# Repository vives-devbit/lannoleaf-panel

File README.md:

# LannooLeaf Panel

| Front | Back |
|---|---|
|  |

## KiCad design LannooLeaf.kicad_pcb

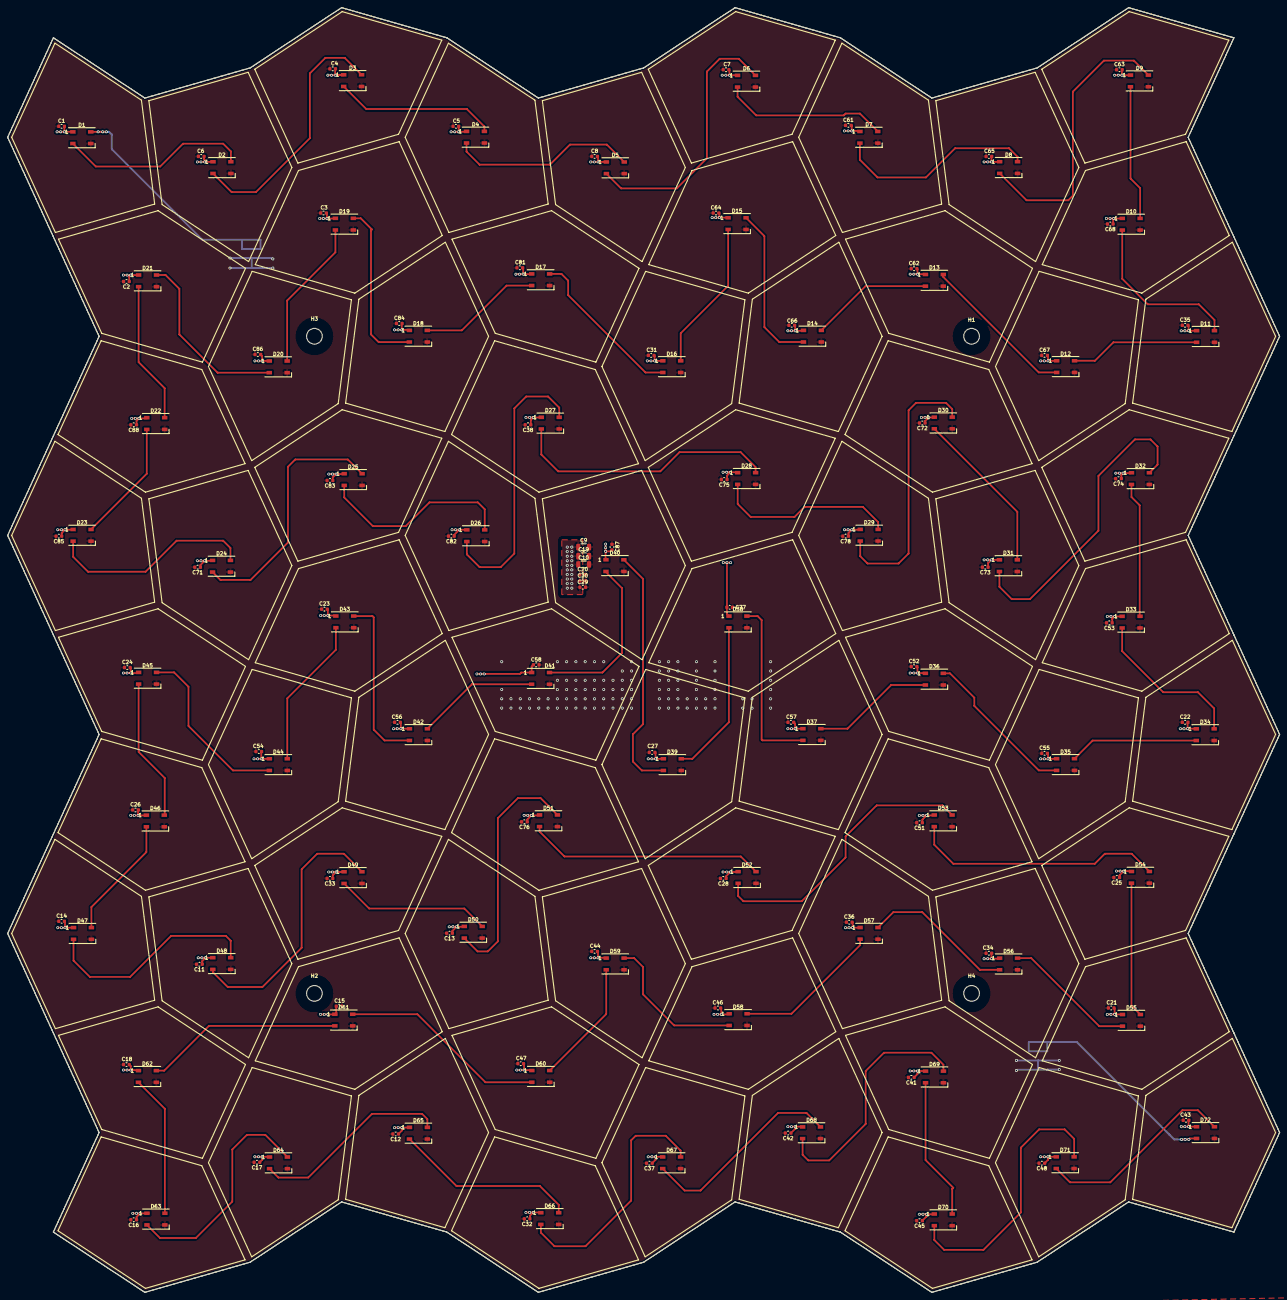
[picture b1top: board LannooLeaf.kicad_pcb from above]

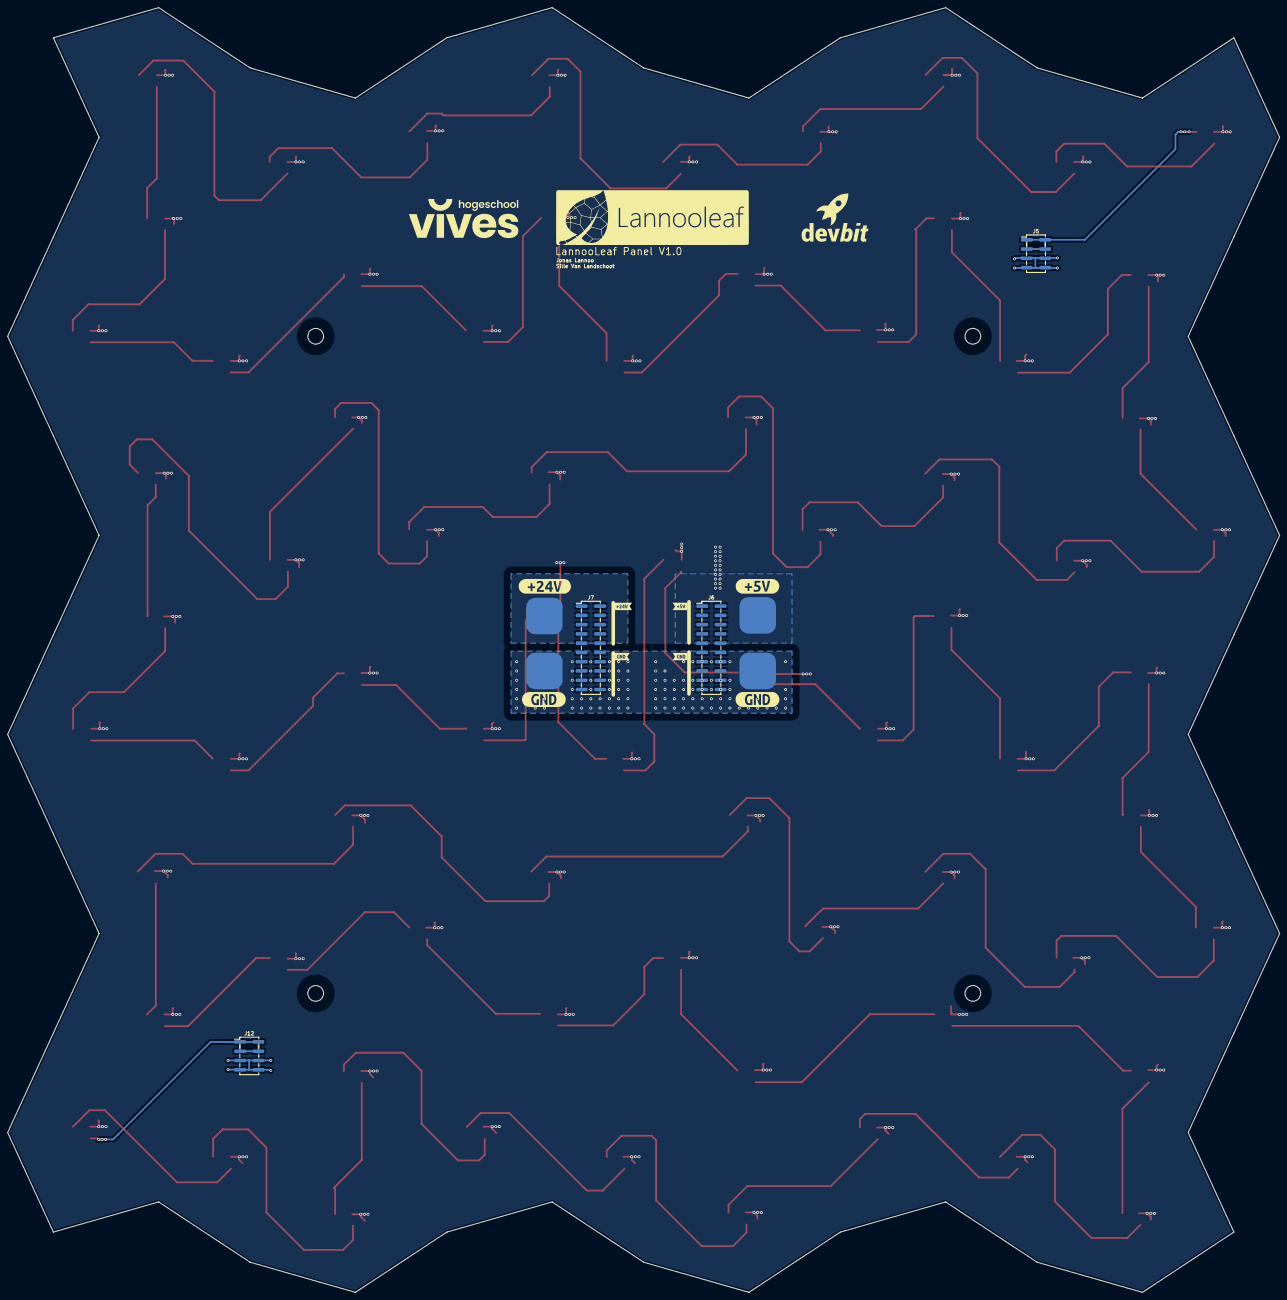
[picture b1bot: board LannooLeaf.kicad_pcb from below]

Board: 2 copper layers, 348.4 x 351.9 mm, 173 parts (19 on the bottom side), 76 nets.

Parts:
C1, C2, C3, C4, C5, C6, C7, C8, C11, C12, C13, C14, C15, C16, C17, C18, C21, C22, C23, C24, C25, C26, C27, C28, C31, C32, C33, C34, C35, C36, C37, C38, C41, C42, C43, C44, C45, C46, C47, C48, C51, C52, C53, C54, C55, C56, C57, C58, C61, C62, C63, C64, C65, C66, C67, C68, C71, C72, C73, C74, C75, C76, C77, C78, C81, C82, C83, C84, C85, C86, C87, C88: 100nF; C_0603_1608Metric
C9, C10, C19: 22uF; C_1206_3216Metric
C20, C29, C30: 1uF; C_0603_1608Metric
D1, D2, D3, D4, D5, D6, D7, D8, D9, D10, D11, D12, D13, D14, D15, D16, D17, D18, D19, D20, D21, D22, D23, D24, D25, D26, D27, D28, D29, D30, D31, D32, D33, D34, D35, D36, D37, D38, D39, D40, D41, D42, D43, D44, D45, D46, D47, D48, D49, D50, D51, D52, D53, D54, D55, D56, D57, D58, D59, D60, D61, D62, D63, D64, D65, D66, D67, D68, D69, D70, D71, D72: WS2812B; LED_WS2812B_PLCC4_5.0x5.0mm_P3.2mm
H1: MountingHole; MountingHole_4.3mm_M4_ISO14580
H2, H3, H4: MountingHole; MountingHole_4.3mm_M4_ISO7380
H5: Logo LannooLeaf; Logo
H6: Logo VIVES; logo-vives
H7: Logo DevBit; logo_devbit_15mm
J1, J2, J3, J4: Conn_01x01; Powerpad
J5, J12: Conn_02x04_Counter_Clockwise; PinHeader_2x04_P2.54mm_Vertical_SMD
J6, J7: Conn_02x10_Counter_Clockwise; PinHeader_2x10_P2.54mm_Vertical_SMD
kibuzzard-62A843C0: G***; kibuzzard-62A843C0
kibuzzard-62A843EA: G***; kibuzzard-62A843EA
kibuzzard-62A8323F: G***; kibuzzard-62A8323F
kibuzzard-62A8324B: G***; kibuzzard-62A8324B
kibuzzard-62A8325B: G***; kibuzzard-62A8325B
kibuzzard-62A8326A: G***; kibuzzard-62A8326A
kibuzzard-62A8440B: G***; kibuzzard-62A8440B
kibuzzard-62A84432: G***; kibuzzard-62A84432

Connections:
+5V: C1.1, C2.1, C3.1, C4.1, C5.1, C6.1, C7.1, C8.1, C9.1, C10.1, C11.1, C12.1, C13.1, C14.1, C15.1, C16.1, C17.1, C18.1, C19.1, C20.1, C21.1, C22.1, C23.1, C24.1, C25.1, C26.1, C27.1, C28.1, C29.1, C30.1, C31.1, C32.1, C33.1, C34.1, C35.1, C36.1, C37.1, C38.1, C41.1, C42.1, C43.1, C44.1, C45.1, C46.1, C47.1, C48.1, C51.1, C52.1, C53.1, C54.1, C55.1, C56.1, C57.1, C58.1, C61.1, C62.1, C63.1, C64.1, C65.1, C66.1, C67.1, C68.1, C71.1, C72.1, C73.1, C74.1, C75.1, C76.1, C77.1, C78.1, C81.1, C82.1, C83.1, C84.1, C85.1, C86.1, C87.1, C88.1, D1.1 (VDD), D2.1 (VDD), D3.1 (VDD), D4.1 (VDD), D5.1 (VDD), D6.1 (VDD), D7.1 (VDD), D8.1 (VDD), D9.1 (VDD), D10.1 (VDD), D11.1 (VDD), D12.1 (VDD), D13.1 (VDD), D14.1 (VDD), D15.1 (VDD), D16.1 (VDD), D17.1 (VDD), D18.1 (VDD), D19.1 (VDD), D20.1 (VDD), D21.1 (VDD), D22.1 (VDD), D23.1 (VDD), D24.1 (VDD), D25.1 (VDD), D26.1 (VDD), D27.1 (VDD), D28.1 (VDD), D29.1 (VDD), D30.1 (VDD), D31.1 (VDD), D32.1 (VDD), D33.1 (VDD), D34.1 (VDD), D35.1 (VDD), D36.1 (VDD), D37.1 (VDD), D38.1 (VDD), D39.1 (VDD), D40.1 (VDD), D41.1 (VDD), D42.1 (VDD), D43.1 (VDD), D44.1 (VDD), D45.1 (VDD), D46.1 (VDD), D47.1 (VDD), D48.1 (VDD), D49.1 (VDD), D50.1 (VDD), D51.1 (VDD), D52.1 (VDD), D53.1 (VDD), D54.1 (VDD), D55.1 (VDD), D56.1 (VDD), D57.1 (VDD), D58.1 (VDD), D59.1 (VDD), D60.1 (VDD), D61.1 (VDD), D62.1 (VDD), D63.1 (VDD), D64.1 (VDD), D65.1 (VDD), D66.1 (VDD), D67.1 (VDD), D68.1 (VDD), D69.1 (VDD), D70.1 (VDD), D71.1 (VDD), D72.1 (VDD), J3.1, J6.1, J6.2, J6.3, J6.4, J6.5, J6.6, J6.7, J6.8, J6.9, J6.10
+24V: J1.1, J7.1, J7.2, J7.3, J7.4, J7.5, J7.6, J7.7, J7.8, J7.9, J7.10
/IN: D1.4 (DIN), J5.1, J5.2, J5.3, J5.4
/OUT: D72.2 (DOUT), J12.1, J12.2, J12.3, J12.4
/Primitive Unit1/OUT: D16.2 (DOUT), D17.4 (DIN)
/Primitive Unit2/OUT: D24.2 (DOUT), D25.4 (DIN)
/Primitive Unit3/OUT: D32.2 (DOUT), D33.4 (DIN)
/Primitive Unit4/OUT: D40.2 (DOUT), D41.4 (DIN)
/Primitive Unit5/IN: D48.2 (DOUT), D49.4 (DIN)
/Primitive Unit5/OUT: D56.2 (DOUT), D57.4 (DIN)
/Primitive Unit6/OUT: D64.2 (DOUT), D65.4 (DIN)
/Primitive Unit/OUT: D8.2 (DOUT), D9.4 (DIN)
GND: C1.2, C2.2, C3.2, C4.2, C5.2, C6.2, C7.2, C8.2, C9.2, C10.2, C11.2, C12.2, C13.2, C14.2, C15.2, C16.2, C17.2, C18.2, C19.2, C20.2, C21.2, C22.2, C23.2, C24.2, C25.2, C26.2, C27.2, C28.2, C29.2, C30.2, C31.2, C32.2, C33.2, C34.2, C35.2, C36.2, C37.2, C38.2, C41.2, C42.2, C43.2, C44.2, C45.2, C46.2, C47.2, C48.2, C51.2, C52.2, C53.2, C54.2, C55.2, C56.2, C57.2, C58.2, C61.2, C62.2, C63.2, C64.2, C65.2, C66.2, C67.2, C68.2, C71.2, C72.2, C73.2, C74.2, C75.2, C76.2, C77.2, C78.2, C81.2, C82.2, C83.2, C84.2, C85.2, C86.2, C87.2, C88.2, D1.3 (VSS), D2.3 (VSS), D3.3 (VSS), D4.3 (VSS), D5.3 (VSS), D6.3 (VSS), D7.3 (VSS), D8.3 (VSS), D9.3 (VSS), D10.3 (VSS), D11.3 (VSS), D12.3 (VSS), D13.3 (VSS), D14.3 (VSS), D15.3 (VSS), D16.3 (VSS), D17.3 (VSS), D18.3 (VSS), D19.3 (VSS), D20.3 (VSS), D21.3 (VSS), D22.3 (VSS), D23.3 (VSS), D24.3 (VSS), D25.3 (VSS), D26.3 (VSS), D27.3 (VSS), D28.3 (VSS), D29.3 (VSS), D30.3 (VSS), D31.3 (VSS), D32.3 (VSS), D33.3 (VSS), D34.3 (VSS), D35.3 (VSS), D36.3 (VSS), D37.3 (VSS), D38.3 (VSS), D39.3 (VSS), D40.3 (VSS), D41.3 (VSS), D42.3 (VSS), D43.3 (VSS), D44.3 (VSS), D45.3 (VSS), D46.3 (VSS), D47.3 (VSS), D48.3 (VSS), D49.3 (VSS), D50.3 (VSS), D51.3 (VSS), D52.3 (VSS), D53.3 (VSS), D54.3 (VSS), D55.3 (VSS), D56.3 (VSS), D57.3 (VSS), D58.3 (VSS), D59.3 (VSS), D60.3 (VSS), D61.3 (VSS), D62.3 (VSS), D63.3 (VSS), D64.3 (VSS), D65.3 (VSS), D66.3 (VSS), D67.3 (VSS), D68.3 (VSS), D69.3 (VSS), D70.3 (VSS), D71.3 (VSS), D72.3 (VSS), J2.1, J4.1, J5.5, J5.6, J5.7, J5.8, J6.11, J6.12, J6.13, J6.14, J6.15, J6.16, J6.17, J6.18, J6.19, J6.20, J7.11, J7.12, J7.13, J7.14, J7.15, J7.16, J7.17, J7.18, J7.19, J7.20, J12.5, J12.6, J12.7, J12.8
unnamed: D1.2 (DOUT), D2.4 (DIN)
unnamed: D2.2 (DOUT), D3.4 (DIN)
unnamed: D3.2 (DOUT), D4.4 (DIN)
unnamed: D4.2 (DOUT), D5.4 (DIN)
unnamed: D5.2 (DOUT), D6.4 (DIN)
unnamed: D6.2 (DOUT), D7.4 (DIN)
unnamed: D7.2 (DOUT), D8.4 (DIN)
unnamed: D10.2 (DOUT), D11.4 (DIN)
unnamed: D9.2 (DOUT), D10.4 (DIN)
unnamed: D11.2 (DOUT), D12.4 (DIN)
unnamed: D12.2 (DOUT), D13.4 (DIN)
unnamed: D13.2 (DOUT), D14.4 (DIN)
unnamed: D14.2 (DOUT), D15.4 (DIN)
unnamed: D15.2 (DOUT), D16.4 (DIN)
unnamed: D17.2 (DOUT), D18.4 (DIN)
unnamed: D18.2 (DOUT), D19.4 (DIN)
unnamed: D19.2 (DOUT), D20.4 (DIN)
unnamed: D20.2 (DOUT), D21.4 (DIN)
unnamed: D21.2 (DOUT), D22.4 (DIN)
unnamed: D22.2 (DOUT), D23.4 (DIN)
unnamed: D23.2 (DOUT), D24.4 (DIN)
unnamed: D25.2 (DOUT), D26.4 (DIN)
unnamed: D26.2 (DOUT), D27.4 (DIN)
unnamed: D27.2 (DOUT), D28.4 (DIN)
unnamed: D28.2 (DOUT), D29.4 (DIN)
unnamed: D29.2 (DOUT), D30.4 (DIN)
unnamed: D30.2 (DOUT), D31.4 (DIN)
unnamed: D31.2 (DOUT), D32.4 (DIN)
unnamed: D33.2 (DOUT), D34.4 (DIN)
unnamed: D34.2 (DOUT), D35.4 (DIN)
unnamed: D35.2 (DOUT), D36.4 (DIN)
unnamed: D36.2 (DOUT), D37.4 (DIN)
unnamed: D37.2 (DOUT), D38.4 (DIN)
unnamed: D38.2 (DOUT), D39.4 (DIN)
unnamed: D39.2 (DOUT), D40.4 (DIN)
unnamed: D41.2 (DOUT), D42.4 (DIN)
unnamed: D42.2 (DOUT), D43.4 (DIN)
unnamed: D43.2 (DOUT), D44.4 (DIN)
unnamed: D44.2 (DOUT), D45.4 (DIN)
unnamed: D45.2 (DOUT), D46.4 (DIN)
unnamed: D46.2 (DOUT), D47.4 (DIN)
unnamed: D47.2 (DOUT), D48.4 (DIN)
unnamed: D49.2 (DOUT), D50.4 (DIN)
unnamed: D50.2 (DOUT), D51.4 (DIN)
unnamed: D51.2 (DOUT), D52.4 (DIN)
unnamed: D52.2 (DOUT), D53.4 (DIN)
unnamed: D53.2 (DOUT), D54.4 (DIN)
unnamed: D54.2 (DOUT), D55.4 (DIN)
unnamed: D55.2 (DOUT), D56.4 (DIN)
unnamed: D57.2 (DOUT), D58.4 (DIN)
unnamed: D58.2 (DOUT), D59.4 (DIN)
unnamed: D59.2 (DOUT), D60.4 (DIN)
unnamed: D60.2 (DOUT), D61.4 (DIN)
unnamed: D61.2 (DOUT), D62.4 (DIN)
unnamed: D62.2 (DOUT), D63.4 (DIN)
unnamed: D63.2 (DOUT), D64.4 (DIN)
unnamed: D65.2 (DOUT), D66.4 (DIN)
unnamed: D66.2 (DOUT), D67.4 (DIN)
unnamed: D67.2 (DOUT), D68.4 (DIN)
unnamed: D68.2 (DOUT), D69.4 (DIN)
unnamed: D69.2 (DOUT), D70.4 (DIN)
unnamed: D70.2 (DOUT), D71.4 (DIN)
unnamed: D71.2 (DOUT), D72.4 (DIN)

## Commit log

2022-06-14 v1.0
2022-06-14 update and fix github actioné
2022-06-14 update mountingholes
2022-06-14 Update generated images
2022-06-14 update labels
2022-06-14 add extra 5V caps
2022-06-17 moved C
    fixes #1
